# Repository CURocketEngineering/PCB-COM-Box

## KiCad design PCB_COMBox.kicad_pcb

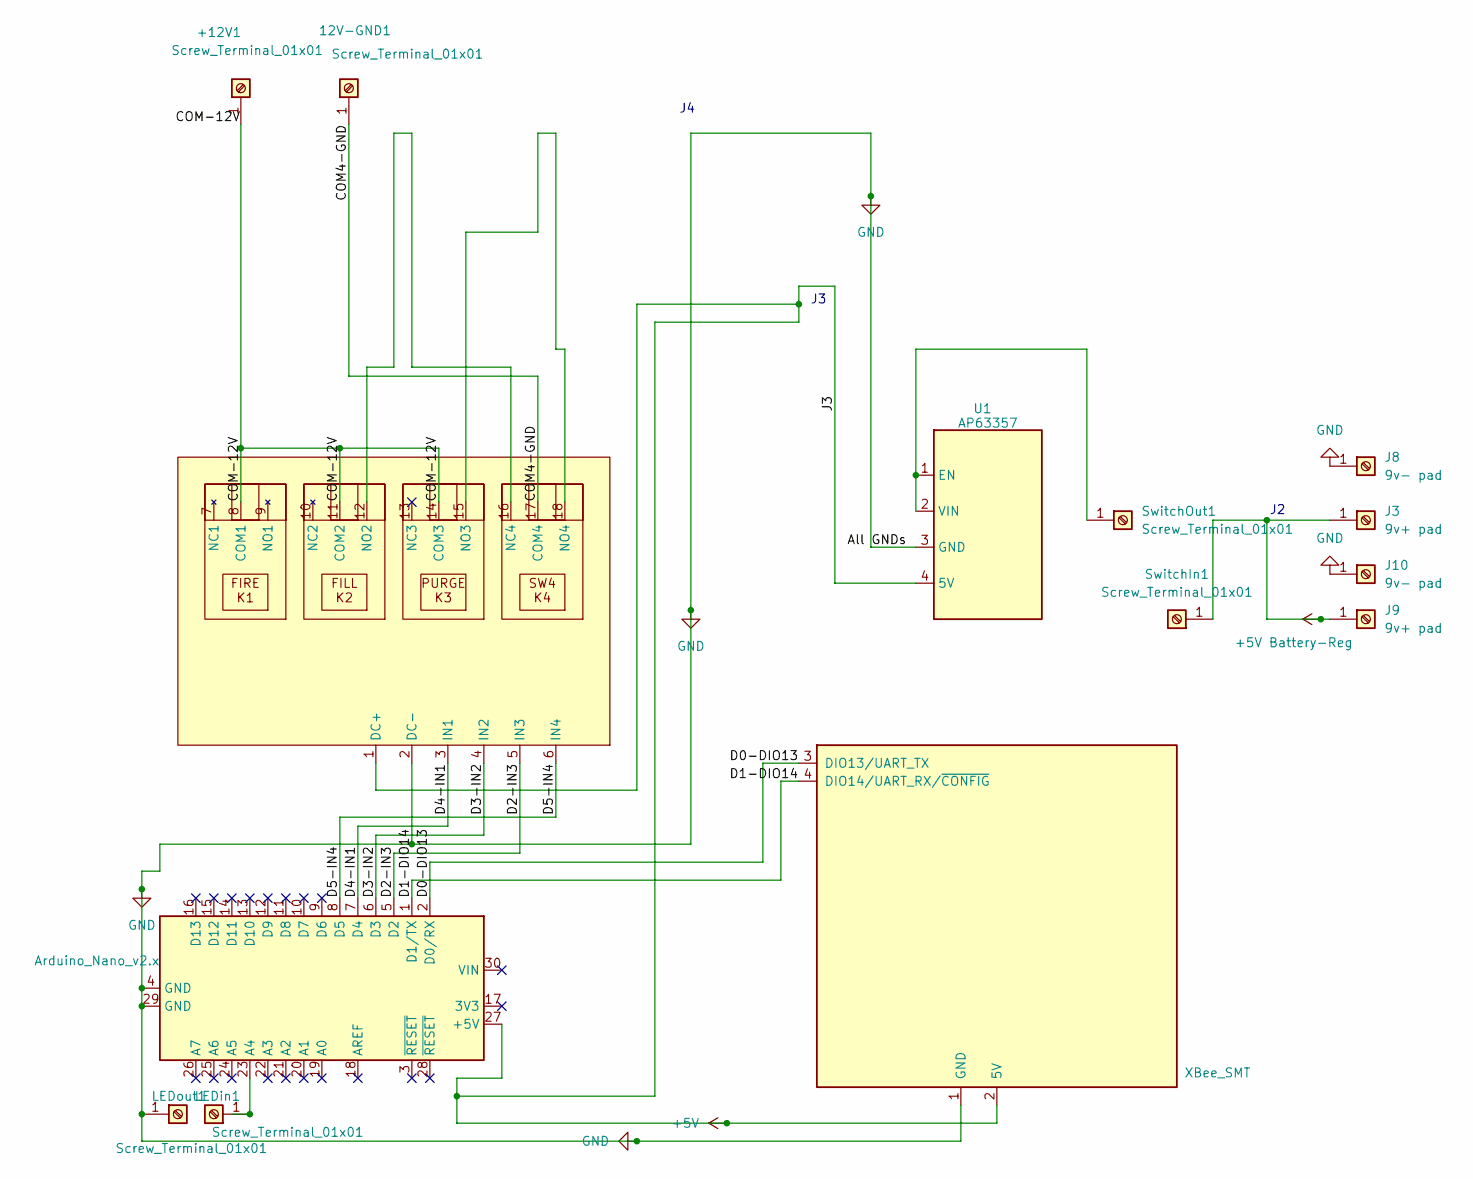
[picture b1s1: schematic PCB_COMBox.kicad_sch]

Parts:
12V-GND1: Screw_Terminal_01x01; ThroughHole
+12V1: Screw_Terminal_01x01; ThroughHole
A1: Arduino_Nano_v2.x; Arduino_Nano
J3, J9: 9v+ pad; SolderPad
J8, J10: 9v- pad; SolderPad
LEDin1: Screw_Terminal_01x01; SolderPad
LEDout1: Screw_Terminal_01x01; SolderPad
SwitchIn1: Screw_Terminal_01x01; SolderPad
SwitchOut1: Screw_Terminal_01x01; SolderPad
U1: AP63357; Reg
U2: Relay
U3: XBee_SMT; Digi_XBee_SMT

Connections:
+5V: A1.27 (+5V), U1.4 (5V), U2.1 (DC+), U3.2 (5V)
+5V Battery-Reg: J3.1, J9.1, SwitchIn1.1
/COM4-GND: 12V-GND1.1, U2.17 (COM4)
/COM-12V: +12V1.1, U2.8 (COM1), U2.11 (COM2), U2.14 (COM3)
/D0-DIO13: A1.2 (D0/RX), U3.3 (DIO13/UART_TX)
/D1-DIO14: A1.1 (D1/TX), U3.4 (DIO14/UART_RX/~CONFIG)
/D2-IN3: A1.5 (D2), U2.5 (IN3)
/D3-IN2: A1.6 (D3), U2.4 (IN2)
/D4-IN1: A1.7 (D4), U2.3 (IN1)
/D5-IN4: A1.8 (D5), U2.6 (IN4)
GND: A1.4 (GND), A1.29 (GND), J8.1, J10.1, LEDout1.1, U1.3 (GND), U2.2 (DC-), U3.1 (GND)
unnamed: A1.23 (A4), LEDin1.1
unnamed: SwitchOut1.1, U1.1 (EN), U1.2 (VIN)
unnamed: U2.12 (NO2), U2.16 (NC4)
unnamed: U2.15 (NO3), U2.18 (NO4)

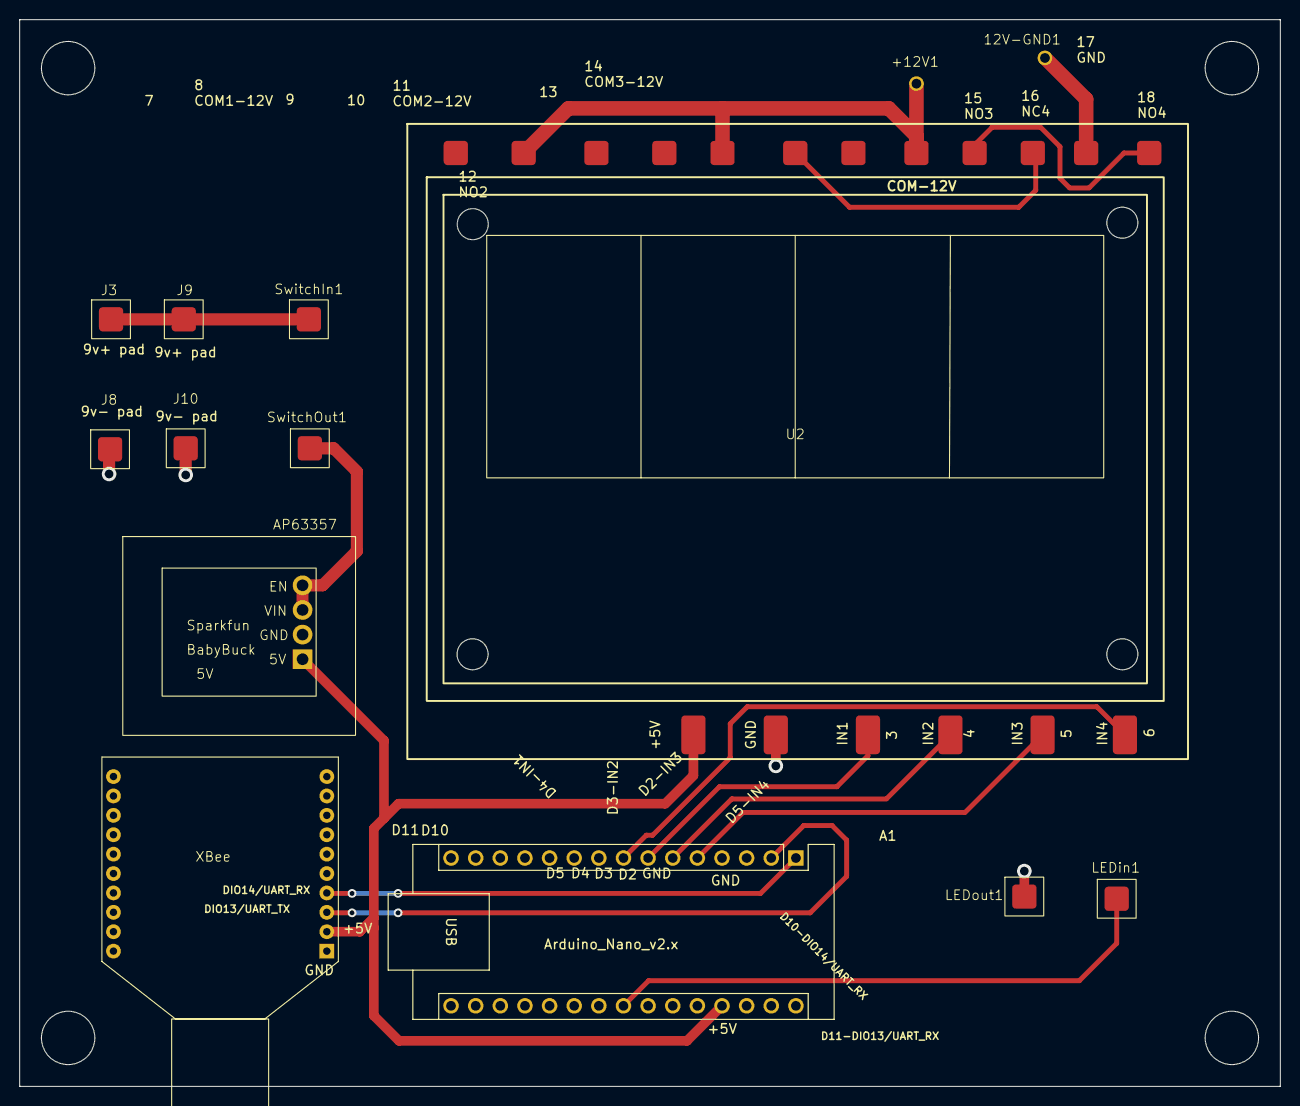
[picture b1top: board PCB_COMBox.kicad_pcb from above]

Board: 2 copper layers, 130.0 x 110.0 mm, 14 parts (0 on the bottom side), 15 nets.

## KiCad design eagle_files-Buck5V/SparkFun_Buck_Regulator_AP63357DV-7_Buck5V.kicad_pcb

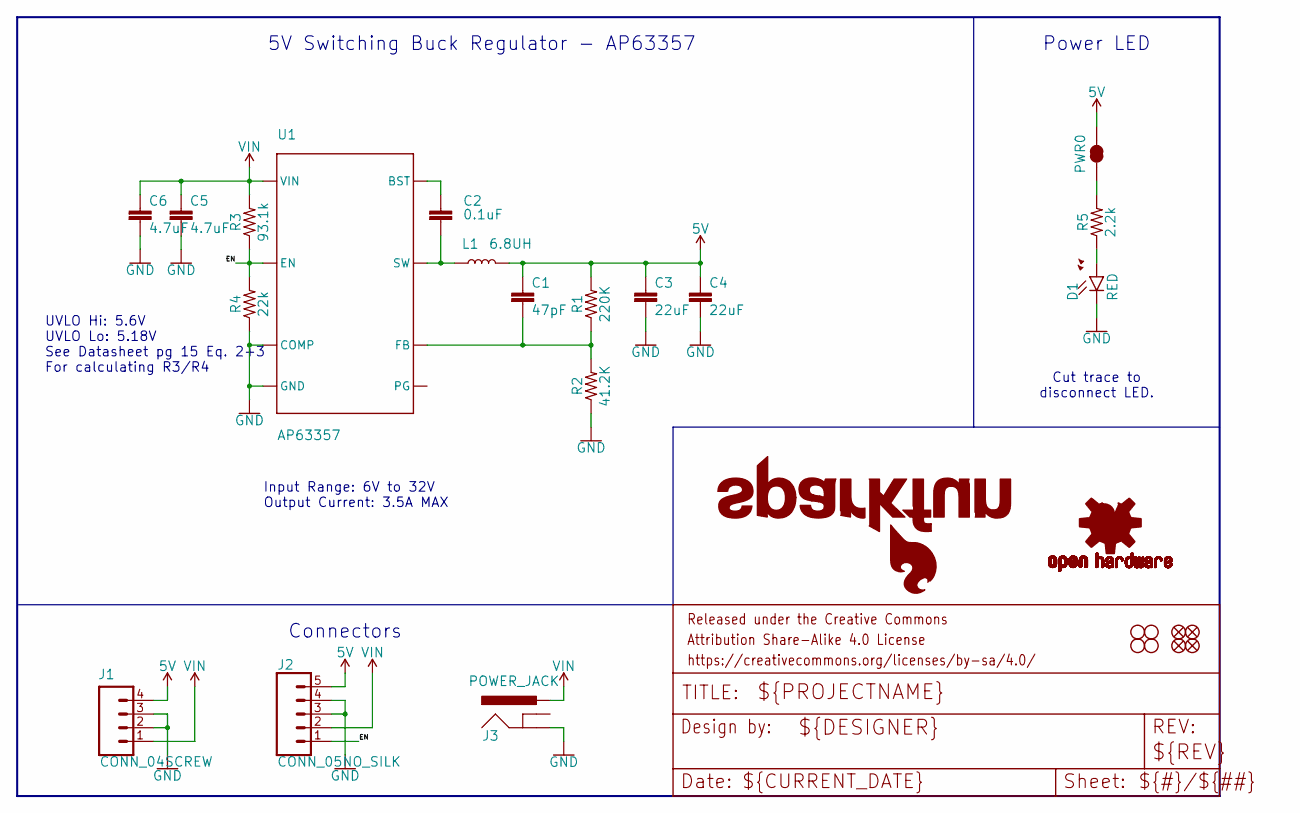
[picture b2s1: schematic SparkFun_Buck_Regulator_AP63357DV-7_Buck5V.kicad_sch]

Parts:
C1: 47pF; 0402-TIGHT
C2: 0.1uF; 0402-TIGHT
C3, C4: 22uF; 0805
C5, C6: 4.7uF; 0805
D1: RED; LED-0603
FD1, FD2, FD3, FD4: FIDUCIALUFIDUCIAL; FIDUCIAL-MICRO
FRAME1: FRAME-LEDGER; CREATIVE_COMMONS
H1, H2, H3, H4: STAND-OFF
J1: CONN_04SCREW; SCREWTERMINAL-3.5MM-4
J2: CONN_05NO_SILK; 1X05_NO_SILK
J3: POWER_JACK; POWER_JACK_PTH_SLOT_NO_OVRHNG_SILK
L1: 6.8UH; 07A7_6U8H
LOGO1: OSHW-LOGOMINI; OSHW-LOGO-MINI
LOGO2: SFE_LOGO_NAME_FLAME.1_INCH; SFE_LOGO_NAME_FLAME_.1
PWR0: JUMPER-SMT_2_NC_TRACE_SILK; SMT-JUMPER_2_NC_TRACE_SILK
R1: 220K; 0402-TIGHT
R2: 41.2K; 0402-TIGHT
R3: 93.1k; 0402-TIGHT
R4: 22k; 0402-TIGHT
R5: 2.2k; 0402-TIGHT
U1: AP63357; V-DFN3020-13

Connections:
5V: C1.1, C3.1, C4.1, J1.4, J2.5, L1.P$2 (2), PWR0.2, R1.2
EN: J2.1, R3.1, R4.2, U1.P$2 (EN)
FB: C1.2, R1.1, R2.2, U1.P$3 (FB)
GND: C3.2, C4.2, C5.2, C6.2, D1.C, J1.2, J1.3, J2.3, J2.4, J3.GND, R2.1, R4.1, U1.P$4 (COMP), U1.P$8 (GND)
unnamed: D1.A, R5.1
unnamed: C2.1, U1.P$6 (BST)
unnamed: PWR0.1, R5.2
SW: C2.2, L1.P$1 (1), U1.P$7 (SW), U1.P$9 (SW)
VIN: C5.1, C6.1, J1.1, J2.2, J3.PWR, R3.2, U1.P$1 (VIN)

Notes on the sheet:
Input Range: 6V to 32V Output Current: 3.5A MAX
Power LED
Connectors
5V Switching Buck Regulator - AP63357
Cut trace to disconnect LED.
UVLO Hi: 5.6V UVLO Lo: 5.18V See Datasheet pg 15 Eq. 2+3 For calculating R3/R4

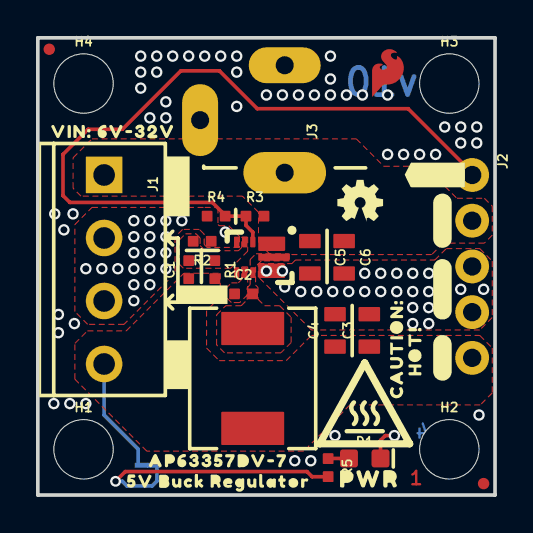
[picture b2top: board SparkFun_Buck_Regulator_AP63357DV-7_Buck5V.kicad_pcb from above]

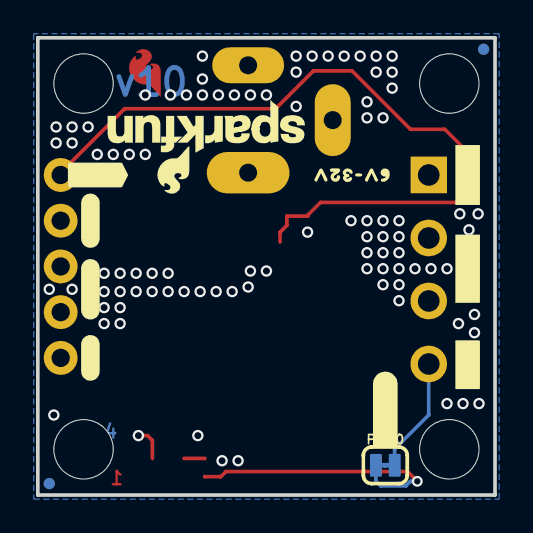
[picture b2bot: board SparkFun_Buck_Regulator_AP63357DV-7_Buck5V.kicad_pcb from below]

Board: 4 copper layers, 25.4 x 25.4 mm, 54 parts (13 on the bottom side), 9 nets.

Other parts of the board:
U$1: AP63357DV#70
U$2: 5V_BUCK_REGULATOR0
U$3: #5V#4
U$4: #VIN#8
U$5, U$13: #VIN#0
U$6, U$7: #GND#0
U$8, U$19: #EN_#0
U$9: #GND#9
U$10: #5V#10
U$11: 6V#32V10
U$12: HOT##0
U$14, U$24: #5V#0
U$15: #LED_#0
U$16: CAUTION#0
U$17: SFE_LOGO_FLAME_COPPER_EXPOSED_.1
U$18: VIN#_6V#32V0
U$20: PWR0
U$21: #GND#1
U$22: HIGH_TEMP_WARNING
U$23: ORDERING_INSTRUCTIONS
U$26: #VIN#3

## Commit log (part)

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2026-01-30 libraries for footprints and schematics
2026-02-06 more files :)
2026-02-13 updated Xbee and Arduino Nano schematics
2026-02-13 new library for relay
2026-02-13 made relay symbol
2026-02-13 created relay and added regulator
2026-02-13 edited a regulator to AP3229/A
2026-02-13 Edited Regulator to AP3429/A
2026-02-13 Update PCB_COMBox.kicad_sch
    edited regulator to AP63357
2026-02-13 AP63357
2026-02-13 feat: Add 5V Buck
2026-02-13 feat: Add 5V-Buck File
    Import non-kicad file
2026-02-17 added xbee back in and trying footprint stuff
2026-02-20 xbee back in, hopefully
2026-02-20 schematic wiring + figuring out connectors (work in progress)
2026-02-27 Added wago connectors
2026-02-27 finished schematic hopefully :)
2026-02-27 schematic changes
2026-02-27 Created Reg Footprint
    Foot
2026-02-27 Actually Created Reg footprint
    feet
2026-02-27 OOOOOOOOOOOOOOOO
2026-03-07 newChangeToday
2026-03-16 Main Branch Commit
    Main branch branch commit commit commit
2026-04-03 Finallyitworks
2026-04-03 feat: add regulator footprint
2026-04-03 feat: add Relay footprint and apply to schematic
    Introduce a new 'Relay' footprint to the custom footprint library to be used within the PCB_COMBox project. Update the schematic to reference this newly added footprint.
2026-04-03 Add custom solder pad footprint and update LED position
    Introduce a new "SolderPad" footprint in CustomFootprints.pretty and update the positioning for an LED component within the PCB_COMBox schematic. These changes are meant to enhance accuracy and organ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
2026-04-04 feat: Add some stuff
2026-04-05 HOORWAYYYYYYYYYYYY
    its done guys
2026-04-06 New changes, Not complete
    Removed sharp corners, updated solder pad footprints. Need to do: make the PCB smaller, add mounting holes
2026-04-10 Fix maybe?
2026-04-10 Fixfix2
2026-04-10 Committing to my changes XOXO
2026-04-10 wswsw
    swswsws
2026-04-10 okwokfqw
    qefqefqefqefqfqfqefqe
2026-04-10 knqufiywgrwbwrg
    rgqgqgq
2026-04-10 net labels + gnd/power labels
2026-04-11 Changeschanged
    dododoodod
2026-04-11 Only relays left
2026-04-13 hole changes dimension changes cleaner look
2026-04-21 heusjamhmduiewgfujmwejuifnjqwkmv
2026-04-21 Final? Maybe?
2026-04-21 22222222
2026-04-23 ThroughPins

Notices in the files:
eagle_files-Buck5V/SparkFun_Buck_Regulator_AP63357DV-7_Buck5V.kicad_sch:
Released under the Creative Commons
https://creativecommons.org/licenses/by-sa/4.0
parts and their libraries:
Released under the Creative Commons Attribution Share-Alike 4.0 License
